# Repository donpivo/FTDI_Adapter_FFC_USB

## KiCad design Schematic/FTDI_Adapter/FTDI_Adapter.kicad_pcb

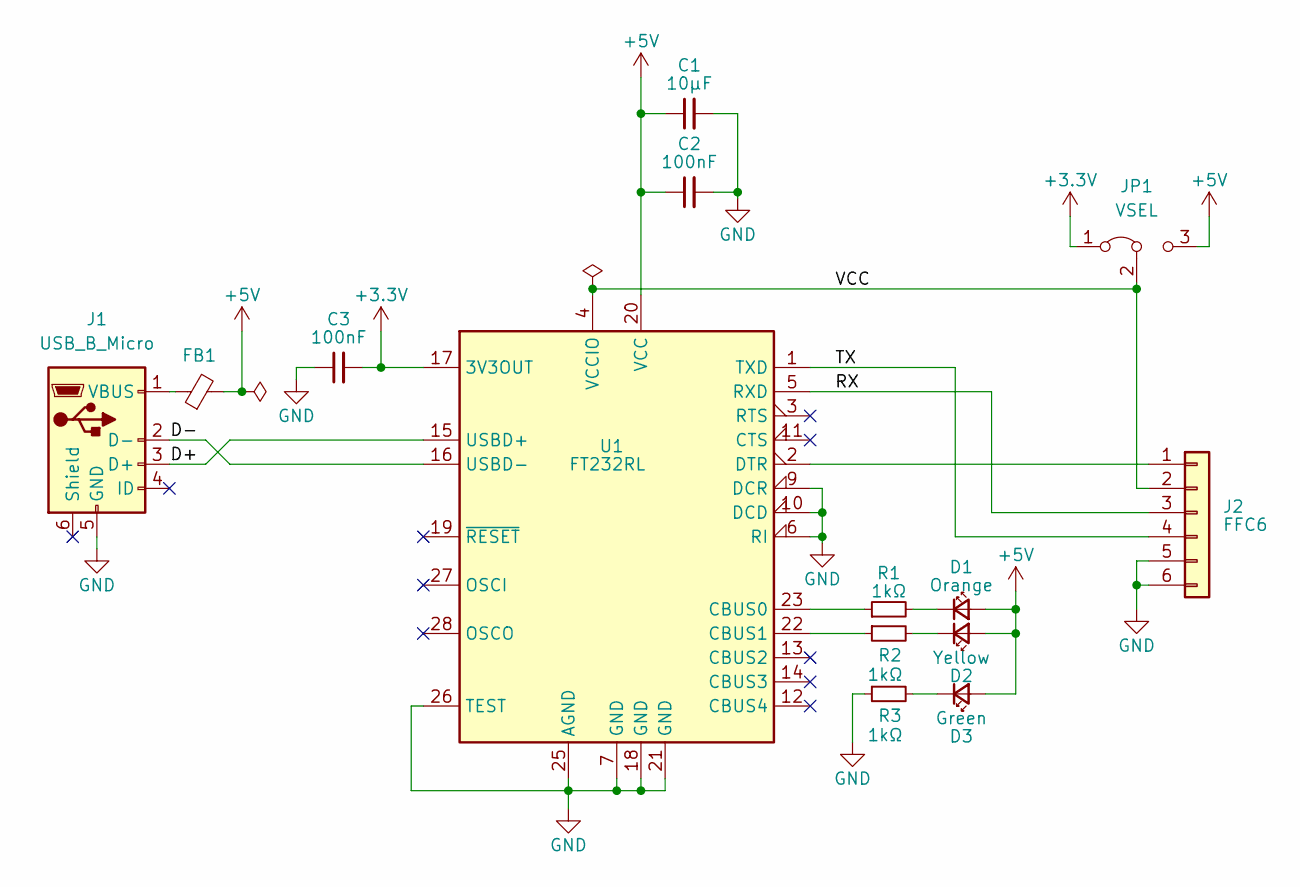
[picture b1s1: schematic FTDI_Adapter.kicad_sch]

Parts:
C1: 10µF; C_0603_1608Metric_Pad1.08x0.95mm_HandSolder
C2, C3: 100nF; C_0603_1608Metric_Pad1.08x0.95mm_HandSolder
D1: Orange; LED_0603_1608Metric_Pad1.05x0.95mm_HandSolder
D2: Yellow; LED_0603_1608Metric_Pad1.05x0.95mm_HandSolder
D3: Green; LED_0603_1608Metric_Pad1.05x0.95mm_HandSolder
FB1: FerriteBead_Small; L_0603_1608Metric_Pad1.05x0.95mm_HandSolder
J1: USB_B_Micro; USB_Micro_B_Female_10118194-0001LF
J2: FFC6; FFC_0527450697
JP1: VSEL; PinHeader_1x03_P1.27mm_Vertical
R1, R2, R3: 1kΩ; R_0603_1608Metric_Pad0.98x0.95mm_HandSolder
U1: FT232RL; SSOP-28_5.3x10.2mm_P0.65mm

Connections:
+3.3V: C3.2, JP1.1 (A), U1.17 (3V3OUT)
+5V: C1.1, C2.1, D1.2 (A), D2.2 (A), D3.2 (A), FB1.2, JP1.3 (B), U1.20 (VCC)
/D+: J1.3 (D+), U1.15 (USBD+)
/D-: J1.2 (D-), U1.16 (USBD-)
/RX: J2.3, U1.5 (RXD)
/TX: J2.4, U1.1 (TXD)
/VCC: J2.2, JP1.2 (C), U1.4 (VCCIO)
GND: C1.2, C2.2, C3.1, J1.5 (GND), J2.5, J2.6, R3.1, U1.6 (RI), U1.7 (GND), U1.9 (DCR), U1.10 (DCD), U1.18 (GND), U1.21 (GND), U1.25 (AGND), U1.26 (TEST)
unnamed: D1.1 (K), R1.2
unnamed: D2.1 (K), R2.2
unnamed: D3.1 (K), R3.2
unnamed: FB1.1, J1.1 (VBUS)
unnamed: J2.1, U1.2 (DTR)
unnamed: R1.1, U1.23 (CBUS0)
unnamed: R2.1, U1.22 (CBUS1)

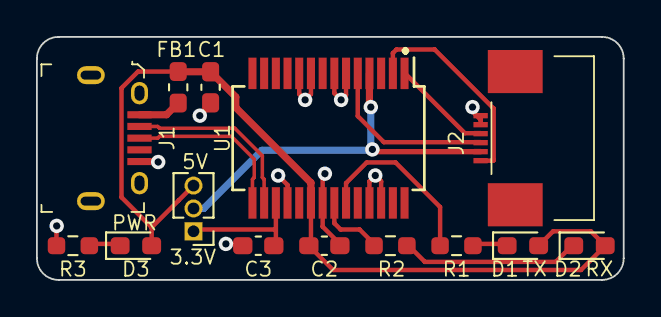
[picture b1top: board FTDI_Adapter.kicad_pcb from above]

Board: 2 copper layers, 32.6 x 13.5 mm, 14 parts (0 on the bottom side), 15 nets.

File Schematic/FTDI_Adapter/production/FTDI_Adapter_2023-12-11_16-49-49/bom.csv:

Designator,Footprint,Quantity,Value,LCSC Part #
"C1, C2",0603,2,100nF,
C3,0603,1,10µF,
D1,0603,1,Orange,
D2,0603,1,Yellow,
D3,0603,1,Green,
FB1,0603,1,FerriteBead_Small,
J1,USB_Micro_B_Female_10118194-0001LF,1,USB_B_Micro,
J2,FFC_0527450697,1,FFC6,
JP1,PinHeader_1x03_P1.27mm_Vertical,1,VSEL,
"R1, R2, R3",0603,3,1kΩ,
U1,SSOP-28_5.3x10.2mm_P0.65mm,1,FT232RL,

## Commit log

2024-02-20 File cleanup
